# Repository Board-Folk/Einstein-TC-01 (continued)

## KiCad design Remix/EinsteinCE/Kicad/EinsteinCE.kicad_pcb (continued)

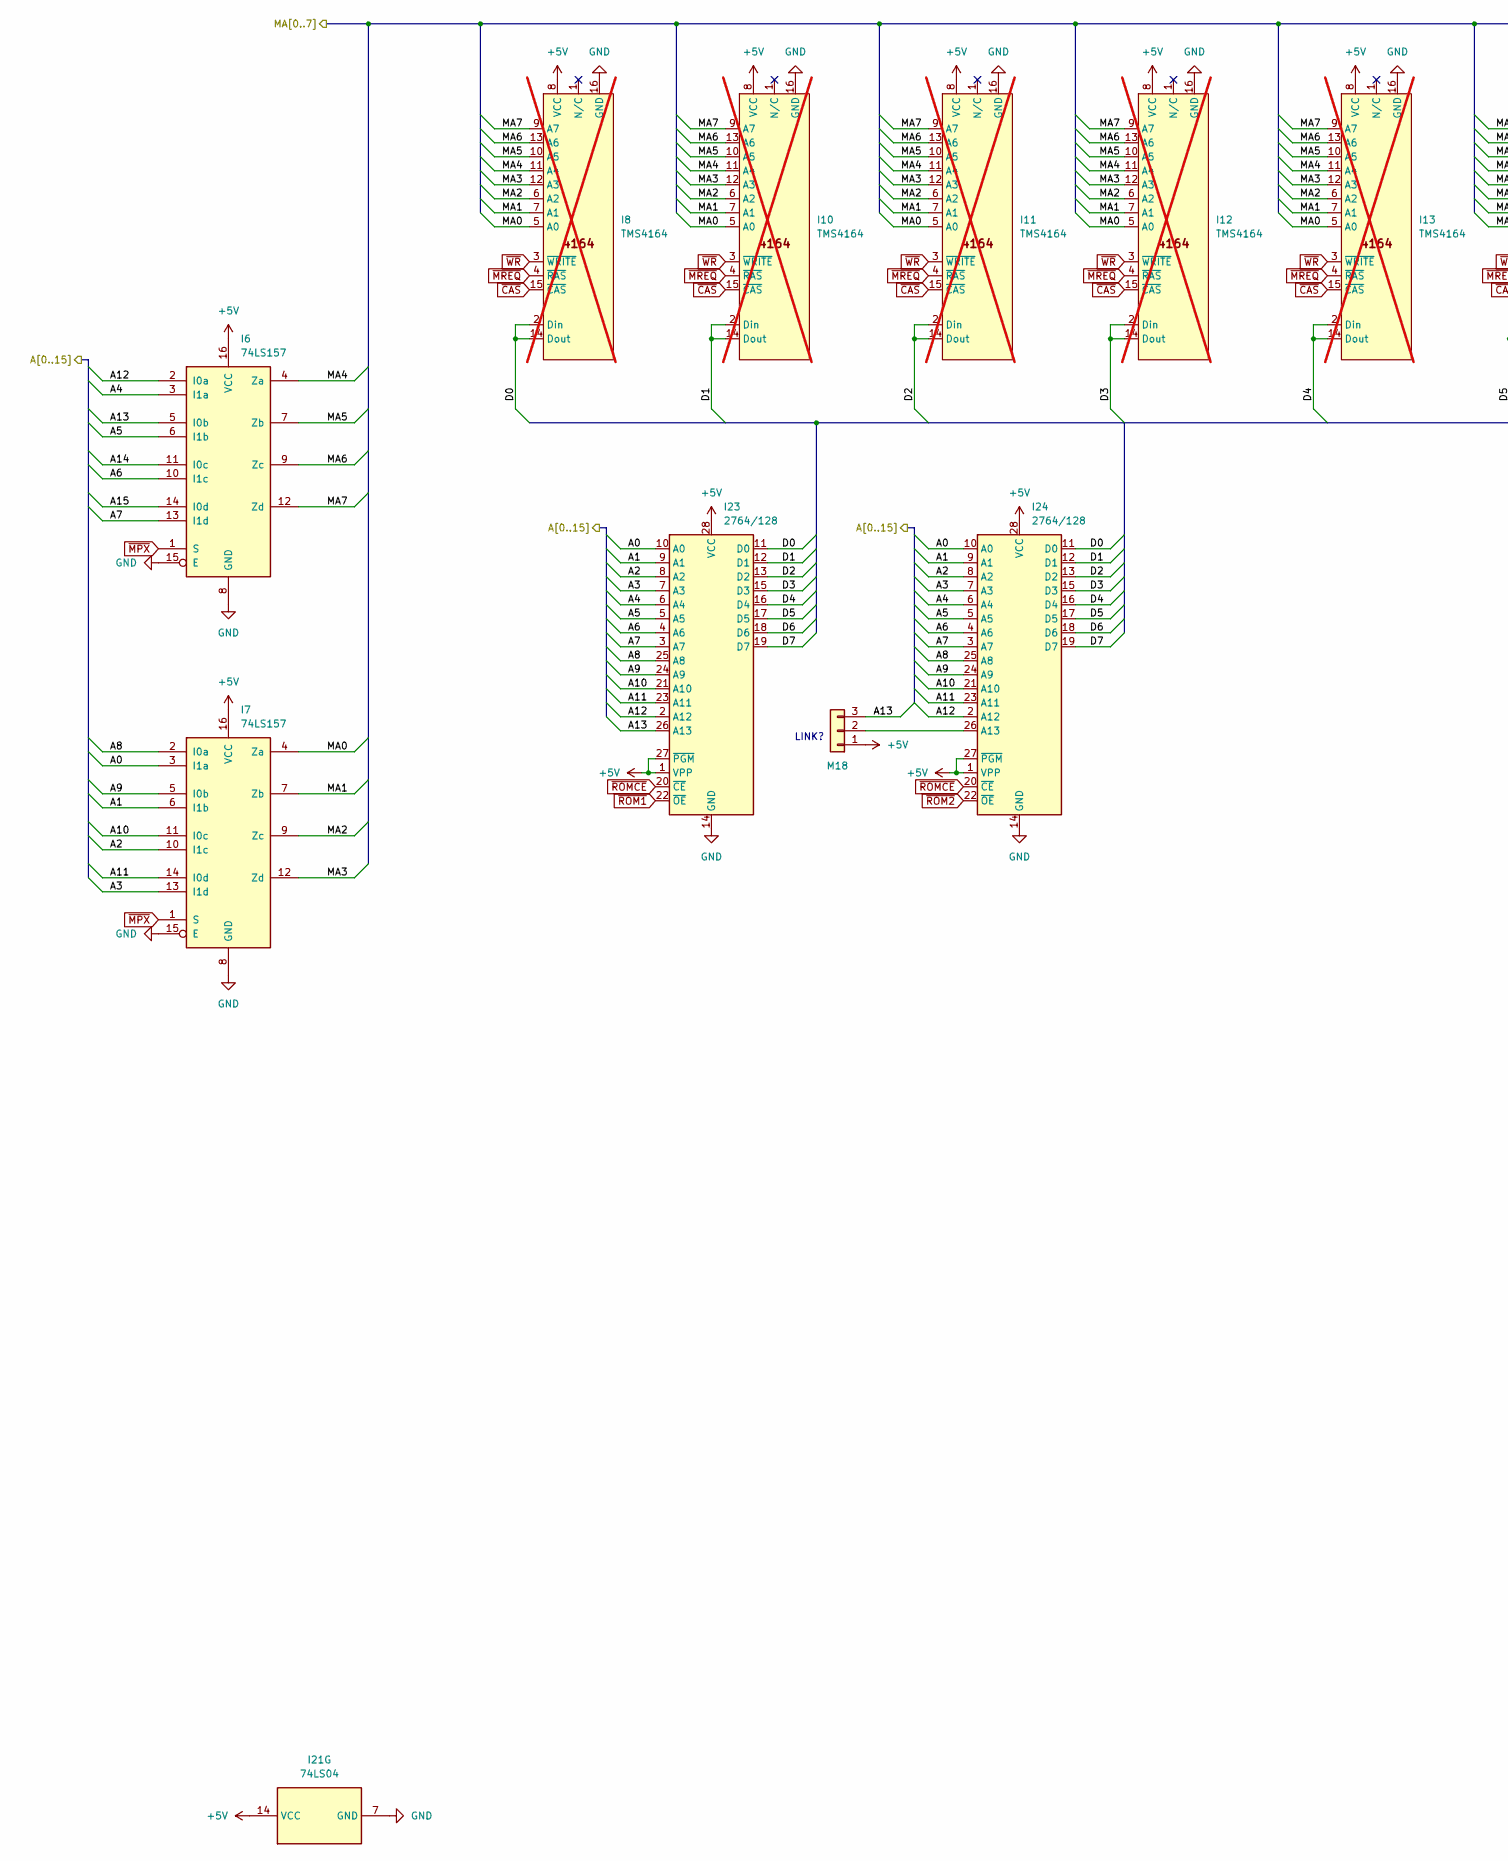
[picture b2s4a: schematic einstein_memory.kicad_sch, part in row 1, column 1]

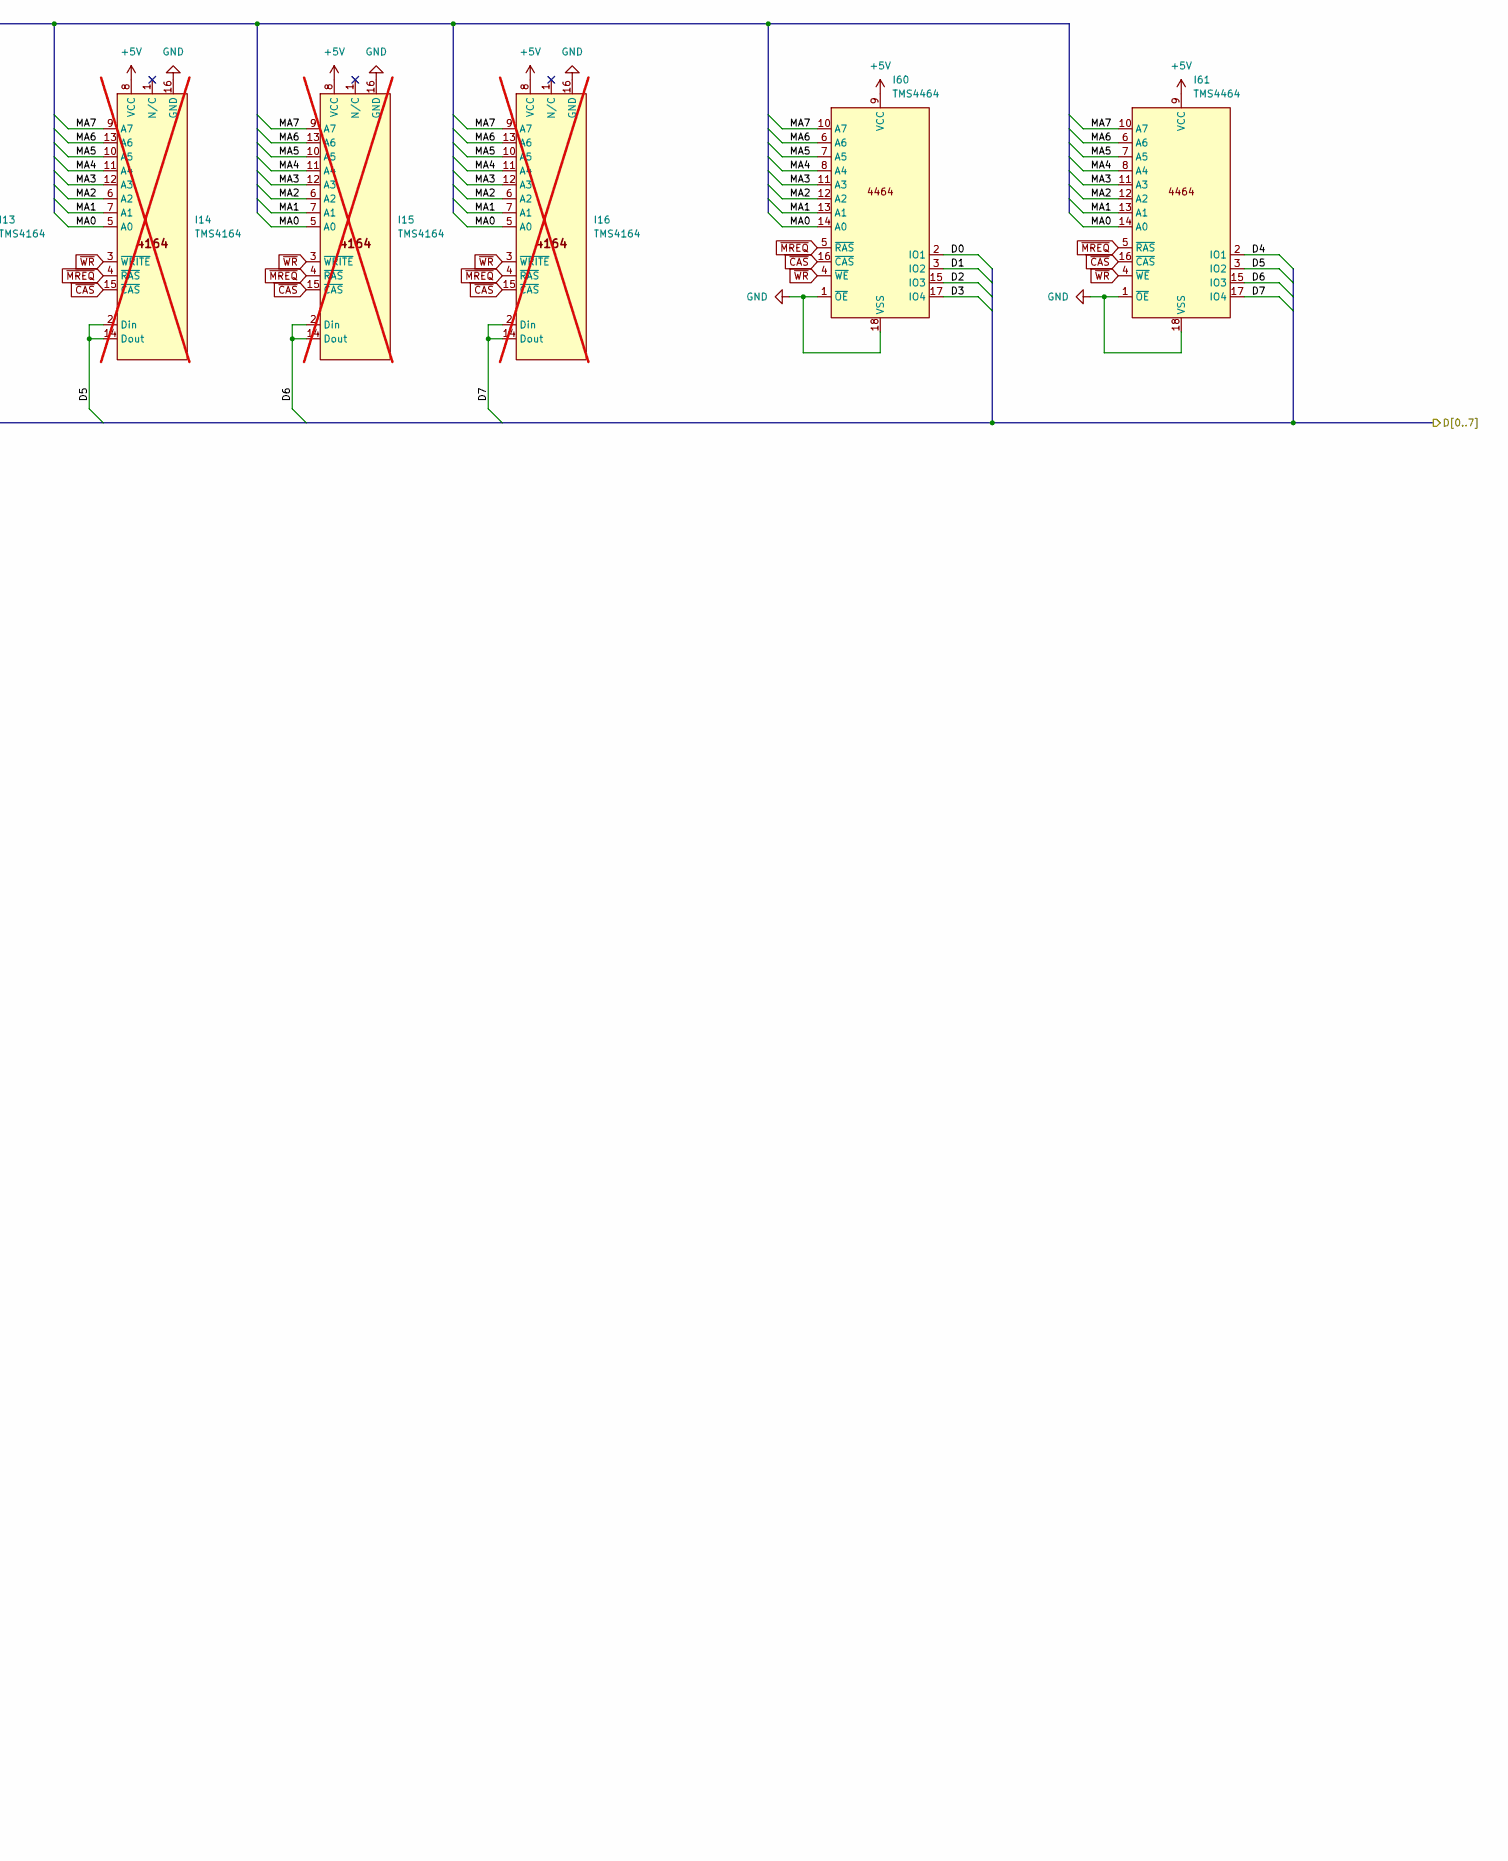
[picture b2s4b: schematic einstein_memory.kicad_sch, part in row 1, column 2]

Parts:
I6, I7: 74LS157; DIP-16_W7.62mm
I8, I10, I11, I12, I13, I14, I15, I16: TMS4164; DIP-16_W7.62mm; not fitted
I21: 74LS04; DIP-14_W7.62mm
I23, I24: 2764/128; DIP-28_W15.24mm
I60, I61: TMS4464; DIP-18_W7.62mm
M18: ROM; M18 PinHeader_1x03_P2.54mm

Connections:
+5V: I6.16 (VCC), I7.16 (VCC), I8.8 (VCC), I10.8 (VCC), I11.8 (VCC), I12.8 (VCC), I13.8 (VCC), I14.8 (VCC), I15.8 (VCC), I16.8 (VCC), I21.14 (VCC), I23.1 (VPP), I23.27 (~PGM), I23.28 (VCC), I24.1 (VPP), I24.27 (~PGM), I24.28 (VCC), I60.9 (VCC), I61.9 (VCC), M18.1; also elsewhere on the board
/Addressing/A0: I7.3 (I1a), I23.10 (A0), I24.10 (A0); also elsewhere on the board
/Addressing/A1: I7.6 (I1b), I23.9 (A1), I24.9 (A1); also elsewhere on the board
/Addressing/A2: I7.10 (I1c), I23.8 (A2), I24.8 (A2); also elsewhere on the board
/Addressing/A3: I7.13 (I1d), I23.7 (A3), I24.7 (A3); also elsewhere on the board
/Addressing/A4: I6.3 (I1a), I23.6 (A4), I24.6 (A4); also elsewhere on the board
/Addressing/A5: I6.6 (I1b), I23.5 (A5), I24.5 (A5); also elsewhere on the board
/Addressing/A6: I6.10 (I1c), I23.4 (A6), I24.4 (A6); also elsewhere on the board
/Addressing/A7: I6.13 (I1d), I23.3 (A7), I24.3 (A7); also elsewhere on the board
/Addressing/A8: I7.2 (I0a), I23.25 (A8), I24.25 (A8); also elsewhere on the board
/Addressing/A9: I7.5 (I0b), I23.24 (A9), I24.24 (A9); also elsewhere on the board
/Addressing/A10: I7.11 (I0c), I23.21 (A10), I24.21 (A10); also elsewhere on the board
/Addressing/A11: I7.14 (I0d), I23.23 (A11), I24.23 (A11); also elsewhere on the board
/Addressing/A12: I6.2 (I0a), I23.2 (A12), I24.2 (A12); also elsewhere on the board
/Addressing/A13: I6.5 (I0b), I23.26 (A13), M18.3; also elsewhere on the board
/Addressing/A14: I6.11 (I0c); also elsewhere on the board
/Addressing/A15: I6.14 (I0d); also elsewhere on the board
/CPU and Buffers/D0: I8.2 (Din), I8.14 (Dout), I23.11 (D0), I24.11 (D0), I60.2 (IO1); also elsewhere on the board
/CPU and Buffers/D1: I10.2 (Din), I10.14 (Dout), I23.12 (D1), I24.12 (D1), I60.3 (IO2); also elsewhere on the board
/CPU and Buffers/D2: I11.2 (Din), I11.14 (Dout), I23.13 (D2), I24.13 (D2), I60.15 (IO3); also elsewhere on the board
/CPU and Buffers/D3: I12.2 (Din), I12.14 (Dout), I23.15 (D3), I24.15 (D3), I60.17 (IO4); also elsewhere on the board
/CPU and Buffers/D4: I13.2 (Din), I13.14 (Dout), I23.16 (D4), I24.16 (D4), I61.2 (IO1); also elsewhere on the board
/CPU and Buffers/D5: I14.2 (Din), I14.14 (Dout), I23.17 (D5), I24.17 (D5), I61.3 (IO2); also elsewhere on the board
/CPU and Buffers/D6: I15.2 (Din), I15.14 (Dout), I23.18 (D6), I24.18 (D6), I61.15 (IO3); also elsewhere on the board
/CPU and Buffers/D7: I16.2 (Din), I16.14 (Dout), I23.19 (D7), I24.19 (D7), I61.17 (IO4); also elsewhere on the board
/System RAM and ROM/MA0: I7.4 (Za), I8.5 (A0), I10.5 (A0), I11.5 (A0), I12.5 (A0), I13.5 (A0), I14.5 (A0), I15.5 (A0), I16.5 (A0), I60.14 (A0), I61.14 (A0)
/System RAM and ROM/MA1: I7.7 (Zb), I8.7 (A1), I10.7 (A1), I11.7 (A1), I12.7 (A1), I13.7 (A1), I14.7 (A1), I15.7 (A1), I16.7 (A1), I60.13 (A1), I61.13 (A1)
/System RAM and ROM/MA2: I7.9 (Zc), I8.6 (A2), I10.6 (A2), I11.6 (A2), I12.6 (A2), I13.6 (A2), I14.6 (A2), I15.6 (A2), I16.6 (A2), I60.12 (A2), I61.12 (A2)
/System RAM and ROM/MA3: I7.12 (Zd), I8.12 (A3), I10.12 (A3), I11.12 (A3), I12.12 (A3), I13.12 (A3), I14.12 (A3), I15.12 (A3), I16.12 (A3), I60.11 (A3), I61.11 (A3)
/System RAM and ROM/MA4: I6.4 (Za), I8.11 (A4), I10.11 (A4), I11.11 (A4), I12.11 (A4), I13.11 (A4), I14.11 (A4), I15.11 (A4), I16.11 (A4), I60.8 (A4), I61.8 (A4)
/System RAM and ROM/MA5: I6.7 (Zb), I8.10 (A5), I10.10 (A5), I11.10 (A5), I12.10 (A5), I13.10 (A5), I14.10 (A5), I15.10 (A5), I16.10 (A5), I60.7 (A5), I61.7 (A5)
/System RAM and ROM/MA6: I6.9 (Zc), I8.13 (A6), I10.13 (A6), I11.13 (A6), I12.13 (A6), I13.13 (A6), I14.13 (A6), I15.13 (A6), I16.13 (A6), I60.6 (A6), I61.6 (A6)
/System RAM and ROM/MA7: I6.12 (Zd), I8.9 (A7), I10.9 (A7), I11.9 (A7), I12.9 (A7), I13.9 (A7), I14.9 (A7), I15.9 (A7), I16.9 (A7), I60.10 (A7), I61.10 (A7)
GND: I6.8 (GND), I6.15 (E), I7.8 (GND), I7.15 (E), I8.16 (GND), I10.16 (GND), I11.16 (GND), I12.16 (GND), I13.16 (GND), I14.16 (GND), I15.16 (GND), I16.16 (GND), I21.7 (GND), I23.14 (GND), I24.14 (GND), I60.1 (~OE), I60.18 (VSS), I61.1 (~OE), I61.18 (VSS); also elsewhere on the board
unnamed: I24.26 (A13), M18.2
~CAS: I8.15 (~CAS), I10.15 (~CAS), I11.15 (~CAS), I12.15 (~CAS), I13.15 (~CAS), I14.15 (~CAS), I15.15 (~CAS), I16.15 (~CAS), I60.16 (~CAS), I61.16 (~CAS); also elsewhere on the board
~MPX: I6.1 (S), I7.1 (S); also elsewhere on the board
~MREQ: I8.4 (~RAS), I10.4 (~RAS), I11.4 (~RAS), I12.4 (~RAS), I13.4 (~RAS), I14.4 (~RAS), I15.4 (~RAS), I16.4 (~RAS), I60.5 (~RAS), I61.5 (~RAS); also elsewhere on the board
~ROM1: I23.22 (~OE); also elsewhere on the board
~ROM2: I24.22 (~OE); also elsewhere on the board
~ROMCE: I23.20 (~CE), I24.20 (~CE); also elsewhere on the board
~WR: I8.3 (~WRITE), I10.3 (~WRITE), I11.3 (~WRITE), I12.3 (~WRITE), I13.3 (~WRITE), I14.3 (~WRITE), I15.3 (~WRITE), I16.3 (~WRITE), I60.4 (~WE), I61.4 (~WE); also elsewhere on the board

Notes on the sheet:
LINK?

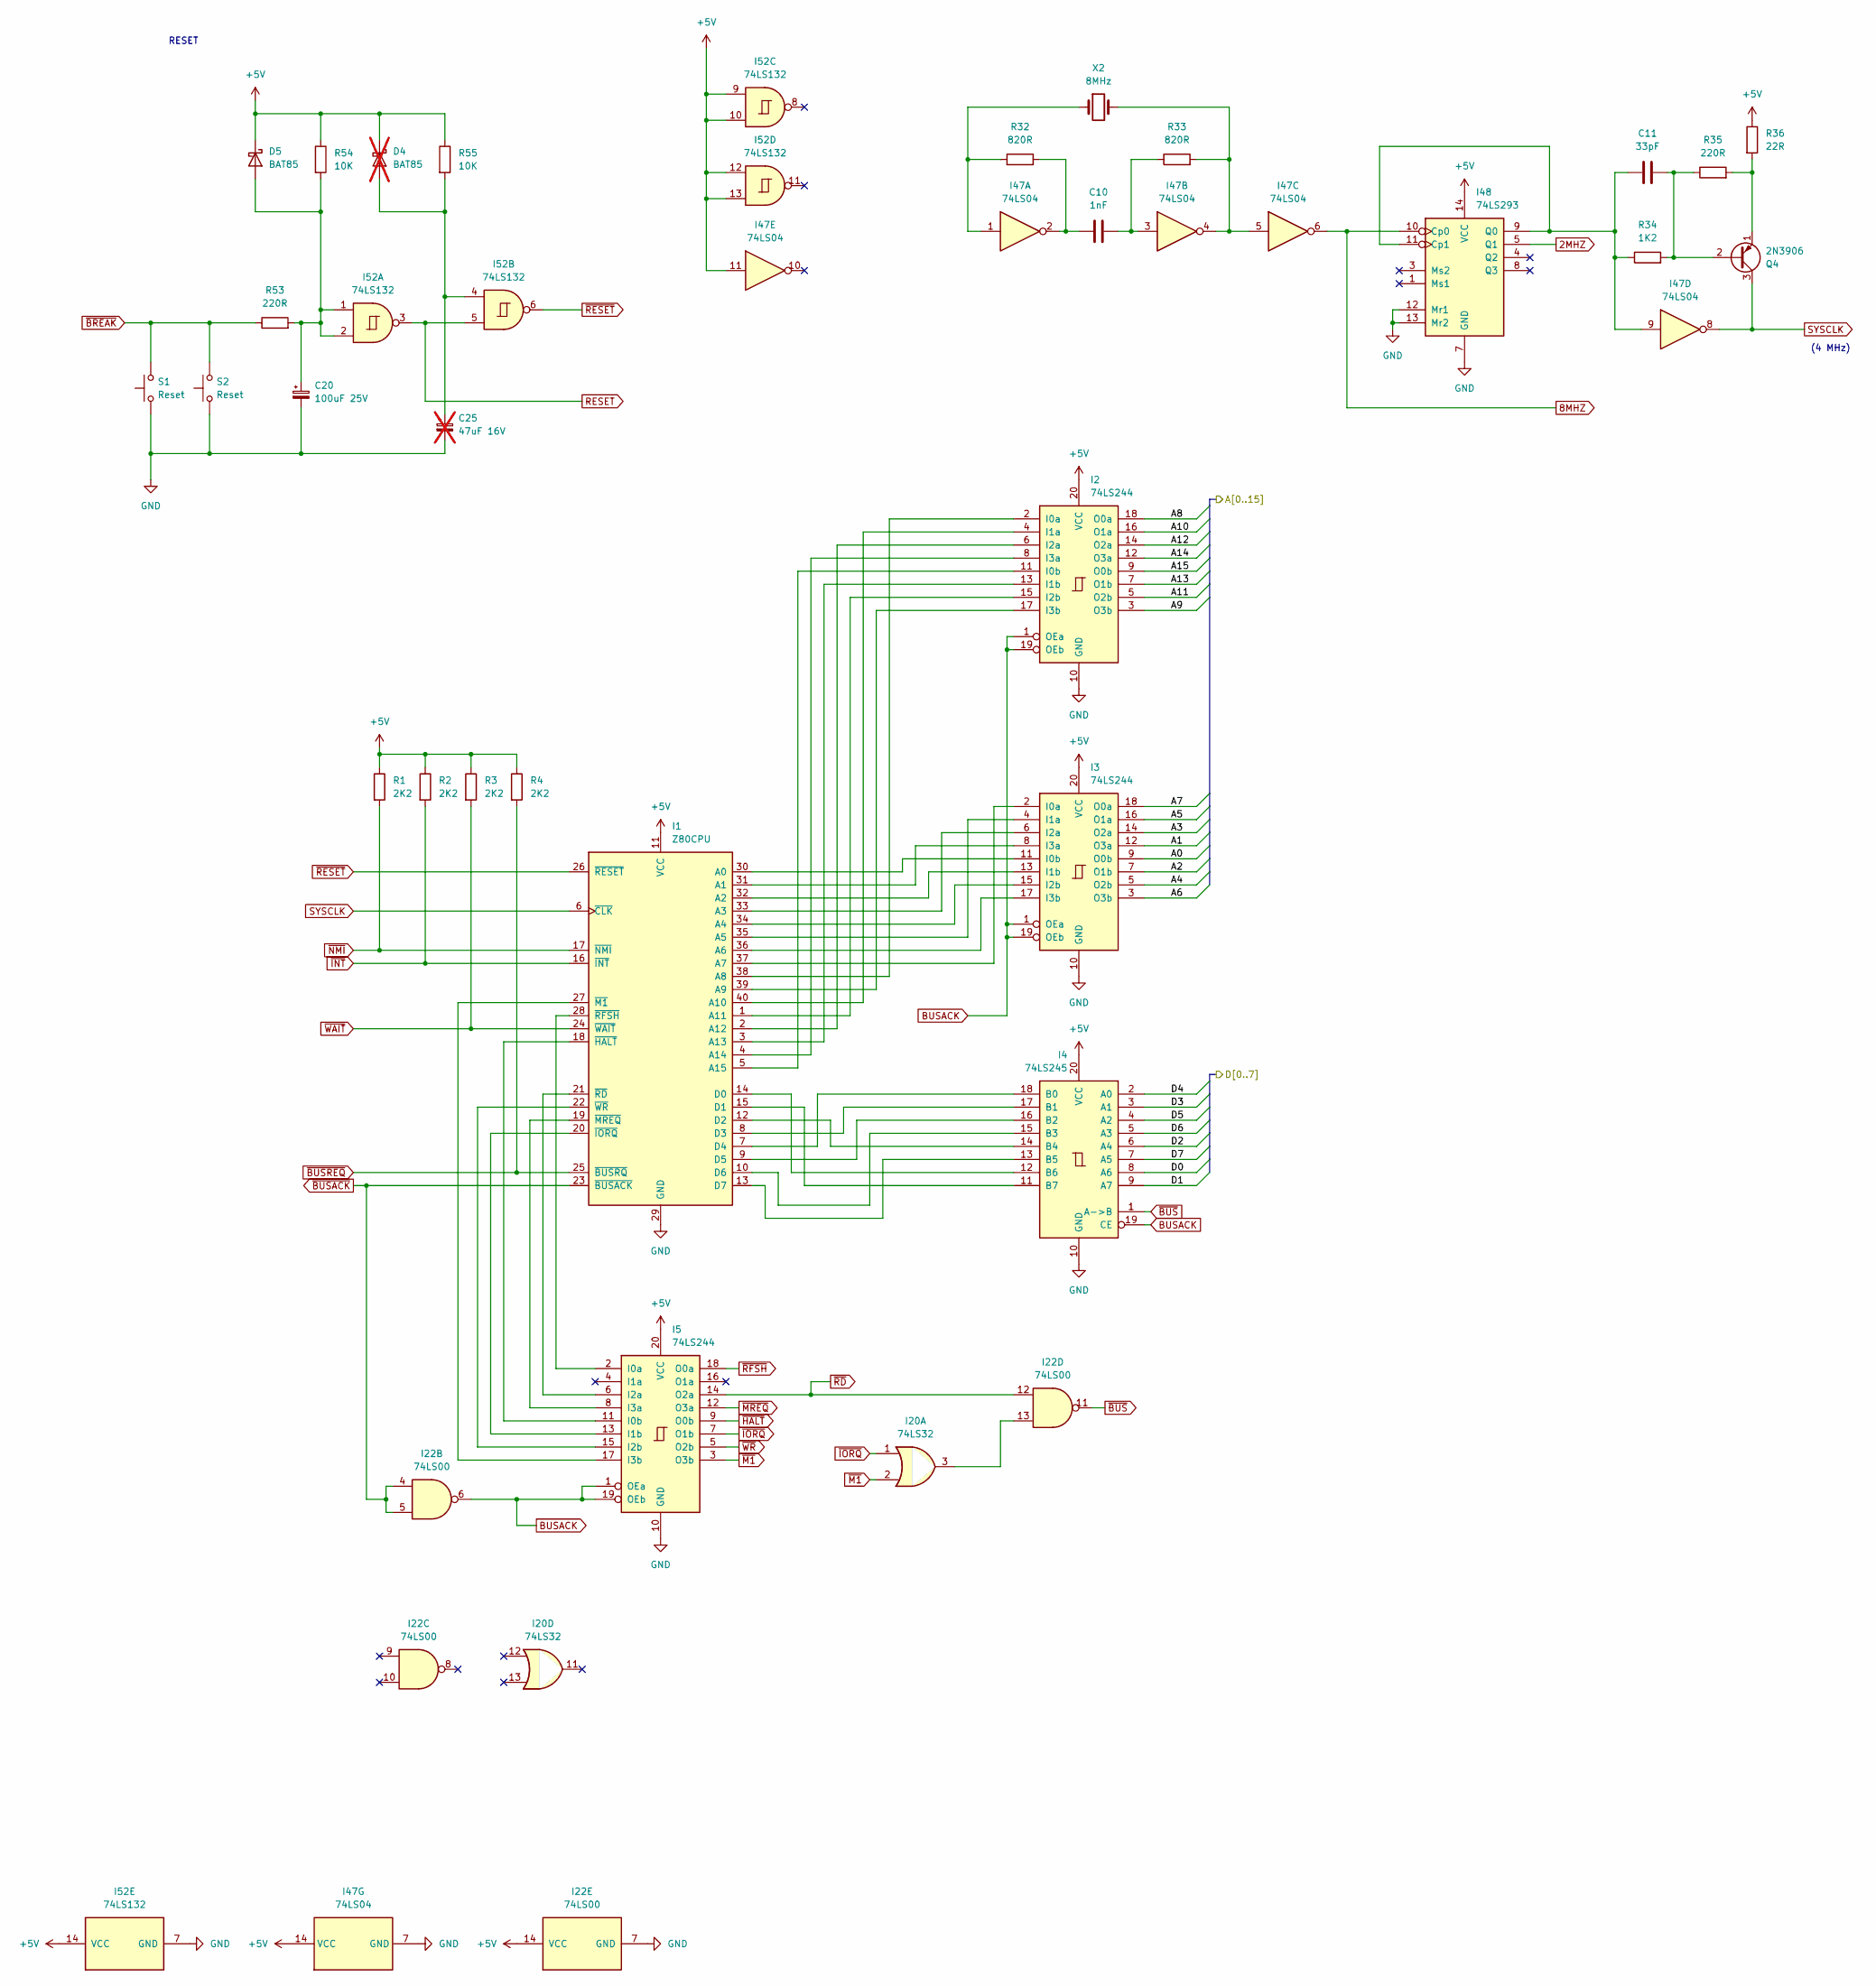
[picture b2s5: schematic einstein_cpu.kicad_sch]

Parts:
C10: 1nF; C_Disc_5.08mm
C11: 33pF; C_Disc_5.08mm
C20: 100uF 25V; Elec_5.08mm - Box
C25: 47uF 16V; Elec_5.08mm - Box; not fitted
D4: BAT85; Diode 10.16mm; not fitted
D5: BAT85; Diode 10.16mm
I1: Z80CPU; DIP-40_W15.24mm
I2, I3, I5: 74LS244; DIP-20_W7.62mm
I4: 74LS245; DIP-20_W7.62mm
I20: 74LS32; DIP-14_W7.62mm
I22: 74LS00; DIP-14_W7.62mm
I47: 74LS04; DIP-14_W7.62mm
I48: 74LS293; DIP-14_W7.62mm
I52: 74LS132; DIP-14_W7.62mm
Q4: 2N3906; Transistor - Box 1 (Alt 1+3) No corner marking
R1, R2, R3, R4: 2K2; Resistor 10.16mm
R32, R33: 820R; Resistor 10.16mm
R34: 1K2; Resistor 10.16mm
R35, R53: 220R; Resistor 10.16mm
R36: 22R; Resistor 10.16mm
R54, R55: 10K; Resistor 10.16mm
S1: Reset; SW_Tactile_SPST_Angled_PTS645Vx58-2LFS_RESET
S2: Reset; LK 2-pin 2.54mm - No Box
X2: 8MHz; Crystal

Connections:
2MHZ: I48.5 (Q1); also elsewhere on the board
8MHZ: I47.6, I48.10 (Cp0); also elsewhere on the board
+5V: D4.1 (K), D5.1 (K), I1.11 (VCC), I2.20 (VCC), I3.20 (VCC), I4.20 (VCC), I5.20 (VCC), I22.14 (VCC), I47.11, I47.14 (VCC), I48.14 (VCC), I52.9, I52.10, I52.12, I52.13, I52.14 (VCC), R1.1, R2.1, R3.1, R4.1, R36.1, R54.1, R55.1; also elsewhere on the board
/Addressing/A0: I3.9 (O0b); also elsewhere on the board
/Addressing/A1: I3.12 (O3a); also elsewhere on the board
/Addressing/A2: I3.7 (O1b); also elsewhere on the board
/Addressing/A3: I3.14 (O2a); also elsewhere on the board
/Addressing/A4: I3.5 (O2b); also elsewhere on the board
/Addressing/A5: I3.16 (O1a); also elsewhere on the board
/Addressing/A6: I3.3 (O3b); also elsewhere on the board
/Addressing/A7: I3.18 (O0a); also elsewhere on the board
/Addressing/A8: I2.18 (O0a); also elsewhere on the board
/Addressing/A9: I2.3 (O3b); also elsewhere on the board
/Addressing/A10: I2.16 (O1a); also elsewhere on the board
/Addressing/A11: I2.5 (O2b); also elsewhere on the board
/Addressing/A12: I2.14 (O2a); also elsewhere on the board
/Addressing/A13: I2.7 (O1b); also elsewhere on the board
/Addressing/A14: I2.12 (O3a); also elsewhere on the board
/Addressing/A15: I2.9 (O0b); also elsewhere on the board
/CPU and Buffers/D0: I4.8 (A6); also elsewhere on the board
/CPU and Buffers/D1: I4.9 (A7); also elsewhere on the board
/CPU and Buffers/D2: I4.6 (A4); also elsewhere on the board
/CPU and Buffers/D3: I4.3 (A1); also elsewhere on the board
/CPU and Buffers/D4: I4.2 (A0); also elsewhere on the board
/CPU and Buffers/D5: I4.4 (A2); also elsewhere on the board
/CPU and Buffers/D6: I4.5 (A3); also elsewhere on the board
/CPU and Buffers/D7: I4.7 (A5); also elsewhere on the board
BUSACK: I2.1 (OEa), I2.19 (OEb), I3.1 (OEa), I3.19 (OEb), I4.19 (CE), I5.1 (OEa), I5.19 (OEb), I22.6
GND: C20.2, C25.2, I1.29 (GND), I2.10 (GND), I3.10 (GND), I4.10 (GND), I5.10 (GND), I22.7 (GND), I47.7 (GND), I48.7 (GND), I48.12 (Mr1), I48.13 (Mr2), I52.7 (GND), S1.1, S2.1; also elsewhere on the board
unnamed: C10.1, I47.3, R33.1
unnamed: C10.2, I47.2, R32.1
unnamed: C25.1, D4.2 (A), I52.4, R55.2
unnamed: C20.1, D5.2 (A), I52.1, I52.2, R53.2, R54.2
unnamed: I1.30 (A0), I3.11 (I0b)
unnamed: I1.31 (A1), I3.8 (I3a)
unnamed: I1.32 (A2), I3.13 (I1b)
unnamed: I1.33 (A3), I3.6 (I2a)
unnamed: I1.34 (A4), I3.15 (I2b)
unnamed: I1.35 (A5), I3.4 (I1a)
unnamed: I1.36 (A6), I3.17 (I3b)
unnamed: I1.37 (A7), I3.2 (I0a)
unnamed: I1.38 (A8), I2.2 (I0a)
unnamed: I1.39 (A9), I2.17 (I3b)
unnamed: I1.40 (A10), I2.4 (I1a)
unnamed: I1.1 (A11), I2.15 (I2b)
unnamed: I1.2 (A12), I2.6 (I2a)
unnamed: I1.3 (A13), I2.13 (I1b)
unnamed: I1.4 (A14), I2.8 (I3a)
unnamed: I1.5 (A15), I2.11 (I0b)
unnamed: I1.14 (D0), I4.12 (B6)
unnamed: I1.15 (D1), I4.11 (B7)
unnamed: I1.12 (D2), I4.14 (B4)
unnamed: I1.8 (D3), I4.17 (B1)
unnamed: I1.7 (D4), I4.18 (B0)
unnamed: I1.9 (D5), I4.16 (B2)
unnamed: I1.10 (D6), I4.15 (B3)
unnamed: I1.13 (D7), I4.13 (B5)
unnamed: I1.18 (~HALT), I5.11 (I0b)
unnamed: I1.20 (~IORQ), I5.13 (I1b)
unnamed: I1.27 (~M1), I5.17 (I3b)
unnamed: I1.19 (~MREQ), I5.8 (I3a)
unnamed: I1.21 (~RD), I5.6 (I2a)
unnamed: I1.28 (~RFSH), I5.2 (I0a)
unnamed: I1.22 (~WR), I5.15 (I2b)
unnamed: I20.3, I22.13
unnamed: I47.1, R32.2, X2.1
unnamed: I47.4, I47.5, R33.2, X2.2
unnamed: C11.2, I47.9, I48.9 (Q0), I48.11 (Cp1), R34.1
unnamed: C11.1, Q4.2 (B), R34.2, R35.1
unnamed: Q4.1 (E), R35.2, R36.2
RESET: I52.3, I52.5; also elsewhere on the board
SYSCLK: I1.6 (~CLK), I47.8, Q4.3 (C); also elsewhere on the board
~BREAK: R53.1, S1.2, S2.2; also elsewhere on the board
~BUSACK: I1.23 (~BUSACK), I22.4, I22.5; also elsewhere on the board
~BUSREQ: I1.25 (~BUSRQ), R4.2; also elsewhere on the board
~BUS: I4.1 (A->B), I22.11
~HALT: I5.9 (O0b); also elsewhere on the board
~INT: I1.16 (~INT), R2.2; also elsewhere on the board
~IORQ: I5.7 (O1b), I20.1; also elsewhere on the board
~M1: I5.3 (O3b), I20.2; also elsewhere on the board
~MREQ: I5.12 (O3a); also elsewhere on the board
~NMI: I1.17 (~NMI), R1.2; also elsewhere on the board
~RD: I5.14 (O2a), I22.12; also elsewhere on the board
~RESET: I1.26 (~RESET), I52.6; also elsewhere on the board
~RFSH: I5.18 (O0a); also elsewhere on the board
~WAIT: I1.24 (~WAIT), R3.2; also elsewhere on the board
~WR: I5.5 (O2b); also elsewhere on the board

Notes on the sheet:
(4 MHz)
RESET

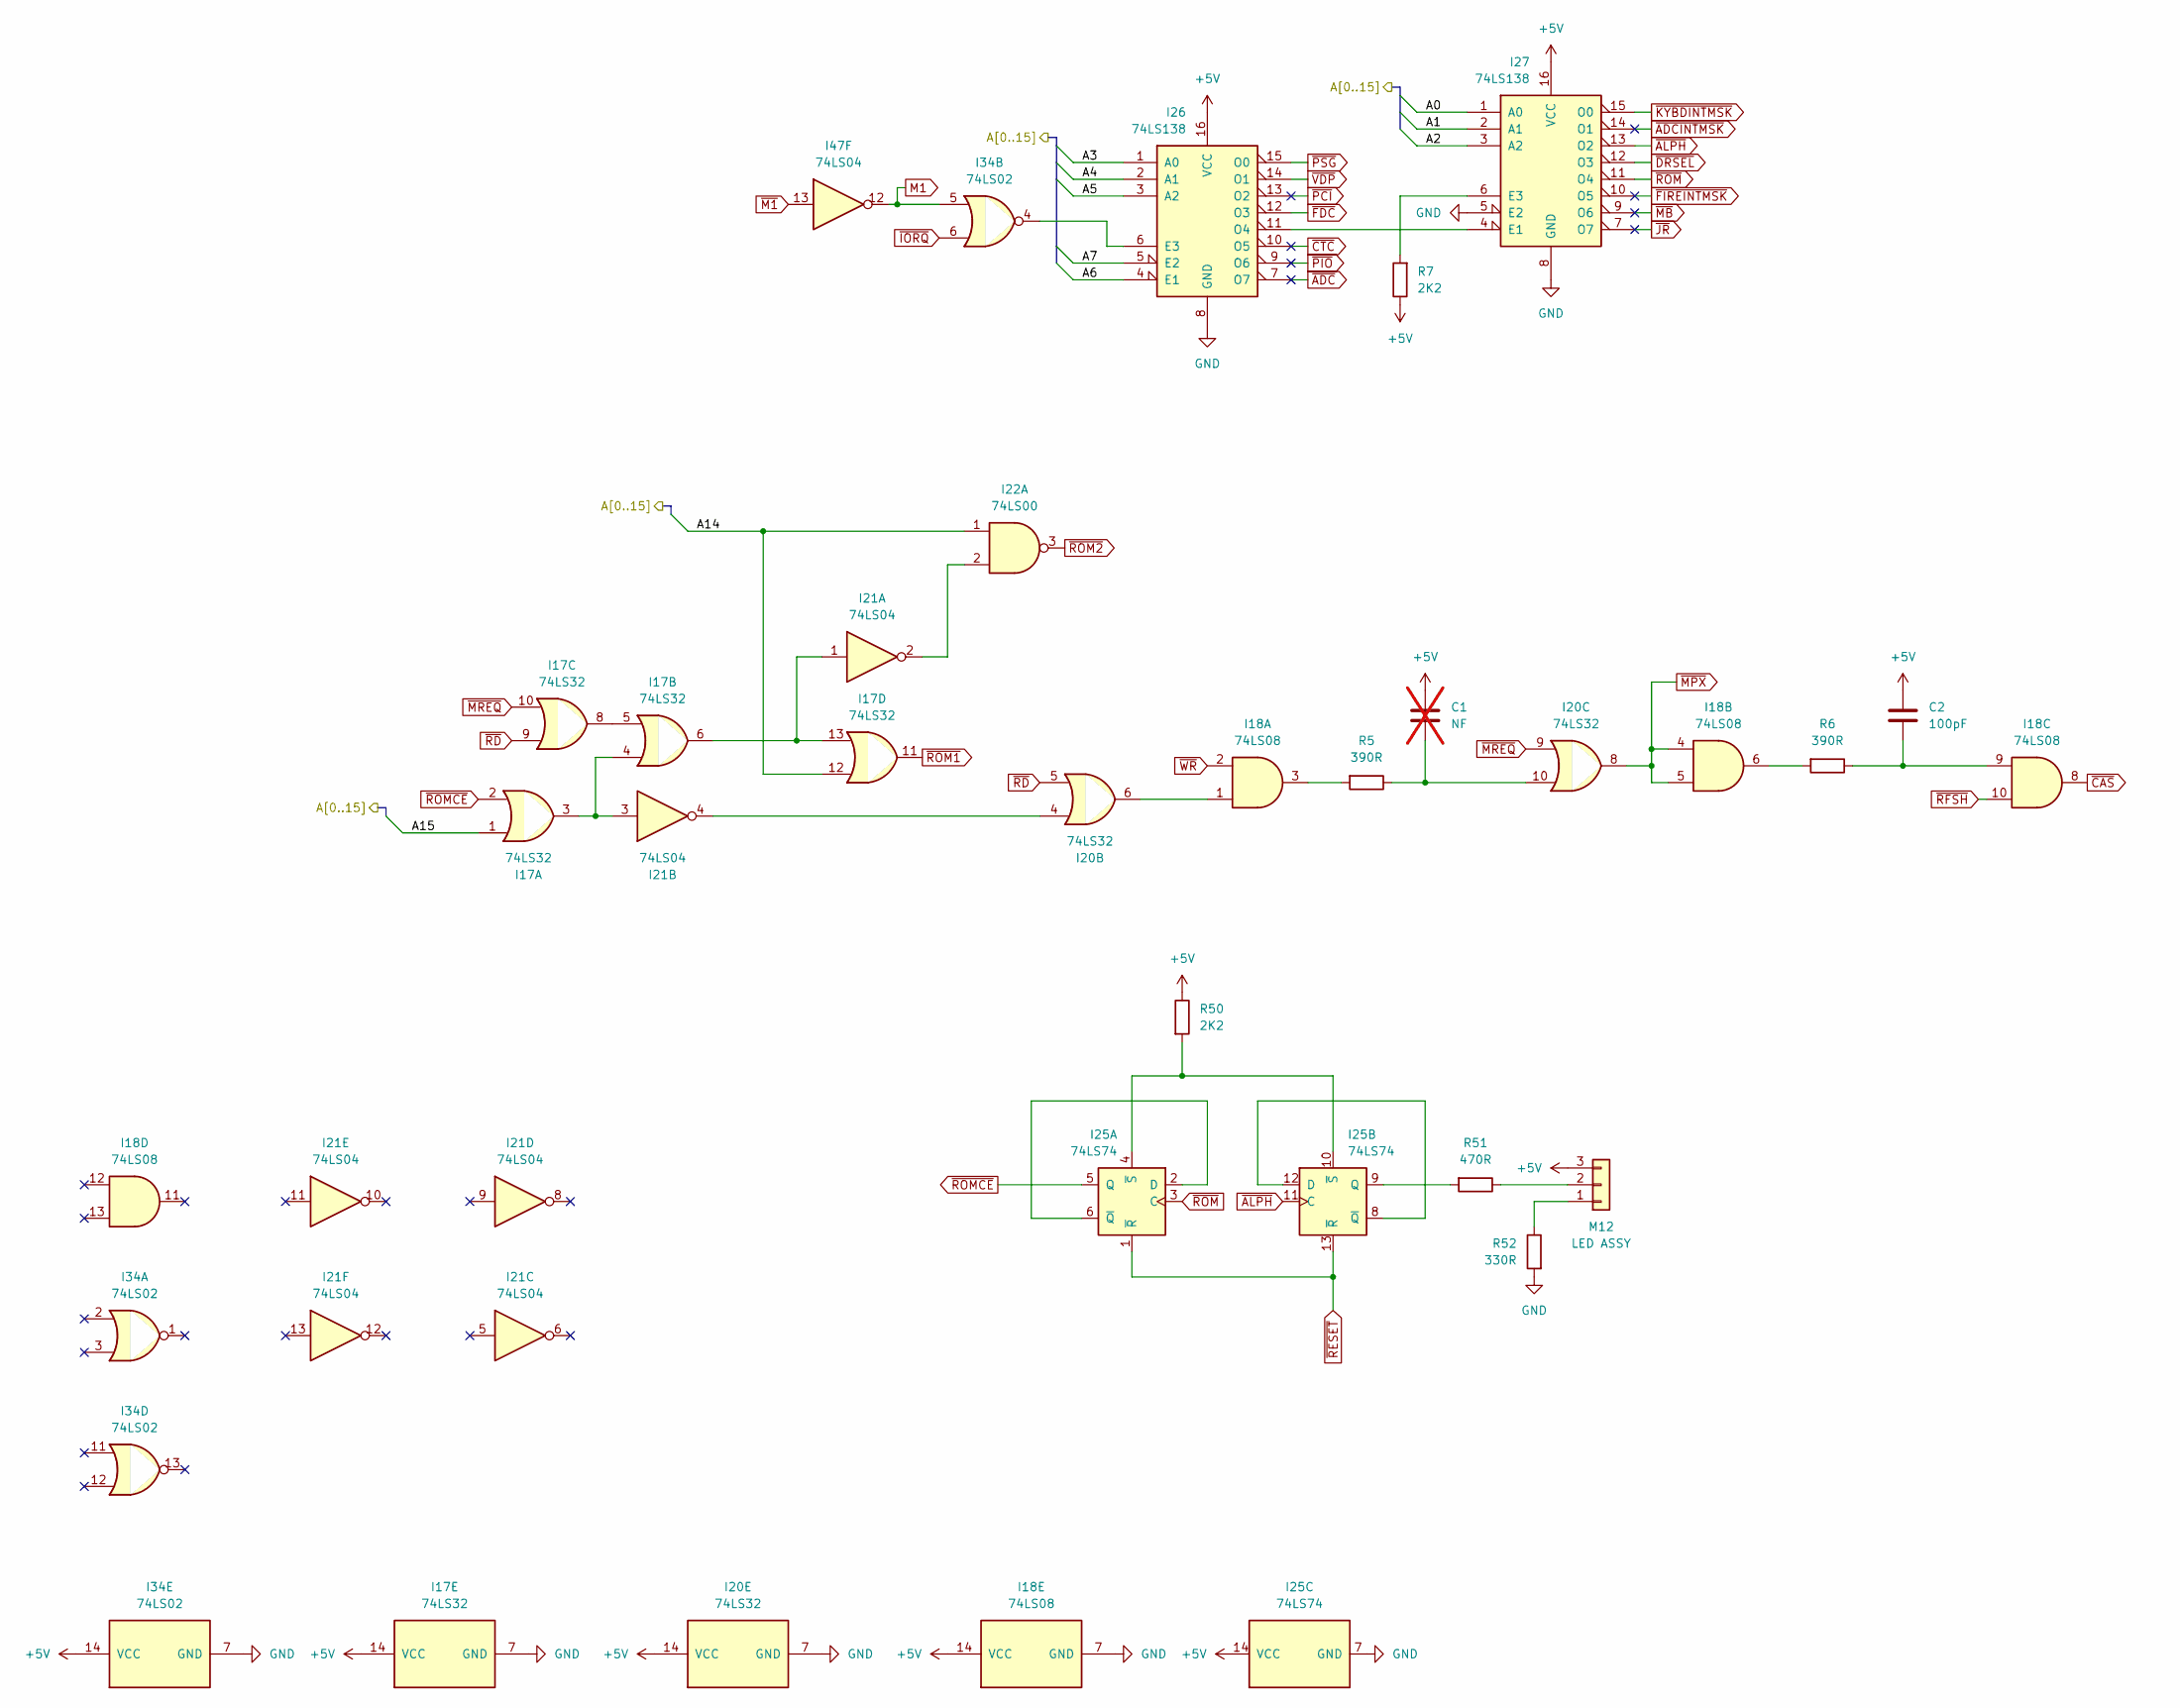
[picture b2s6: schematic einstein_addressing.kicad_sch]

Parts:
C1: NF; C_Disc_5.08mm; not fitted
C2: 100pF; C_Disc_5.08mm
I17, I20: 74LS32; DIP-14_W7.62mm
I18: 74LS08; DIP-14_W7.62mm
I21, I47: 74LS04; DIP-14_W7.62mm
I22: 74LS00; DIP-14_W7.62mm
I25: 74LS74; DIP-14_W7.62mm
I26, I27: 74LS138; DIP-16_W7.62mm
I34: 74LS02; DIP-14_W7.62mm
M12: LED ASSY; M12 PinHeader_1x03_P2.54mm
R5, R6: 390R; Resistor 10.16mm
R7, R50: 2K2; Resistor 10.16mm
R51: 470R; Resistor 10.16mm
R52: 330R; Resistor 10.16mm

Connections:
+5V: C1.1, C2.1, I17.14 (VCC), I18.14 (VCC), I20.14 (VCC), I25.14 (VCC), I26.16 (VCC), I27.16 (VCC), I34.14 (VCC), M12.3, R7.1, R50.1; also elsewhere on the board
/Addressing/A0: I27.1 (A0); also elsewhere on the board
/Addressing/A1: I27.2 (A1); also elsewhere on the board
/Addressing/A2: I27.3 (A2); also elsewhere on the board
/Addressing/A3: I26.1 (A0); also elsewhere on the board
/Addressing/A4: I26.2 (A1); also elsewhere on the board
/Addressing/A5: I26.3 (A2); also elsewhere on the board
/Addressing/A6: I26.4 (E1); also elsewhere on the board
/Addressing/A7: I26.5 (E2); also elsewhere on the board
/Addressing/A14: I17.12, I22.1; also elsewhere on the board
/Addressing/A15: I17.1; also elsewhere on the board
GND: I17.7 (GND), I18.7 (GND), I20.7 (GND), I25.7 (GND), I26.8 (GND), I27.5 (E2), I27.8 (GND), I34.7 (GND), R52.2; also elsewhere on the board
M1: I34.5, I47.12
unnamed: C1.2, I20.10, R5.1
unnamed: C2.2, I18.9, R6.1
unnamed: I17.3, I17.4, I21.3
unnamed: I17.5, I17.8
unnamed: I17.6, I17.13, I21.1
unnamed: I18.1, I20.6
unnamed: I18.3, R5.2
unnamed: I18.6, R6.2
unnamed: I20.4, I21.4
unnamed: I21.2, I22.2
unnamed: I25.2 (D), I25.6 (~Q)
unnamed: I25.4 (~S), I25.10 (~S), R50.2
unnamed: I25.8 (~Q), I25.12 (D)
unnamed: I25.9 (Q), R51.2
unnamed: I26.6 (E3), I34.4
unnamed: I26.11 (O4), I27.4 (E1)
unnamed: I27.6 (E3), R7.2
unnamed: M12.1, R52.1
unnamed: M12.2, R51.1
~ADCINTMSK: I27.14 (O1)
~ADC: I26.7 (O7)
~ALPH: I25.11 (C), I27.13 (O2)
~CAS: I18.8; also elsewhere on the board
~CTC: I26.10 (O5)
~DRSEL: I27.12 (O3); also elsewhere on the board
~FDC: I26.12 (O3); also elsewhere on the board
~FIREINTMSK: I27.10 (O5)
~IORQ: I34.6; also elsewhere on the board
~JR: I27.7 (O7)
~KYBDINTMSK: I27.15 (O0); also elsewhere on the board
~M1: I47.13; also elsewhere on the board
~MB: I27.9 (O6)
~MPX: I18.4, I18.5, I20.8; also elsewhere on the board
~MREQ: I17.10, I20.9; also elsewhere on the board
~PCI: I26.13 (O2)
~PIO: I26.9 (O6)
~PSG: I26.15 (O0); also elsewhere on the board
~RD: I17.9, I20.5; also elsewhere on the board
~RESET: I25.1 (~R), I25.13 (~R); also elsewhere on the board
~RFSH: I18.10; also elsewhere on the board
~ROM1: I17.11; also elsewhere on the board
~ROM2: I22.3; also elsewhere on the board
~ROMCE: I17.2, I25.5 (Q); also elsewhere on the board
~ROM: I25.3 (C), I27.11 (O4)
~VDP: I26.14 (O1); also elsewhere on the board
~WR: I18.2; also elsewhere on the board
